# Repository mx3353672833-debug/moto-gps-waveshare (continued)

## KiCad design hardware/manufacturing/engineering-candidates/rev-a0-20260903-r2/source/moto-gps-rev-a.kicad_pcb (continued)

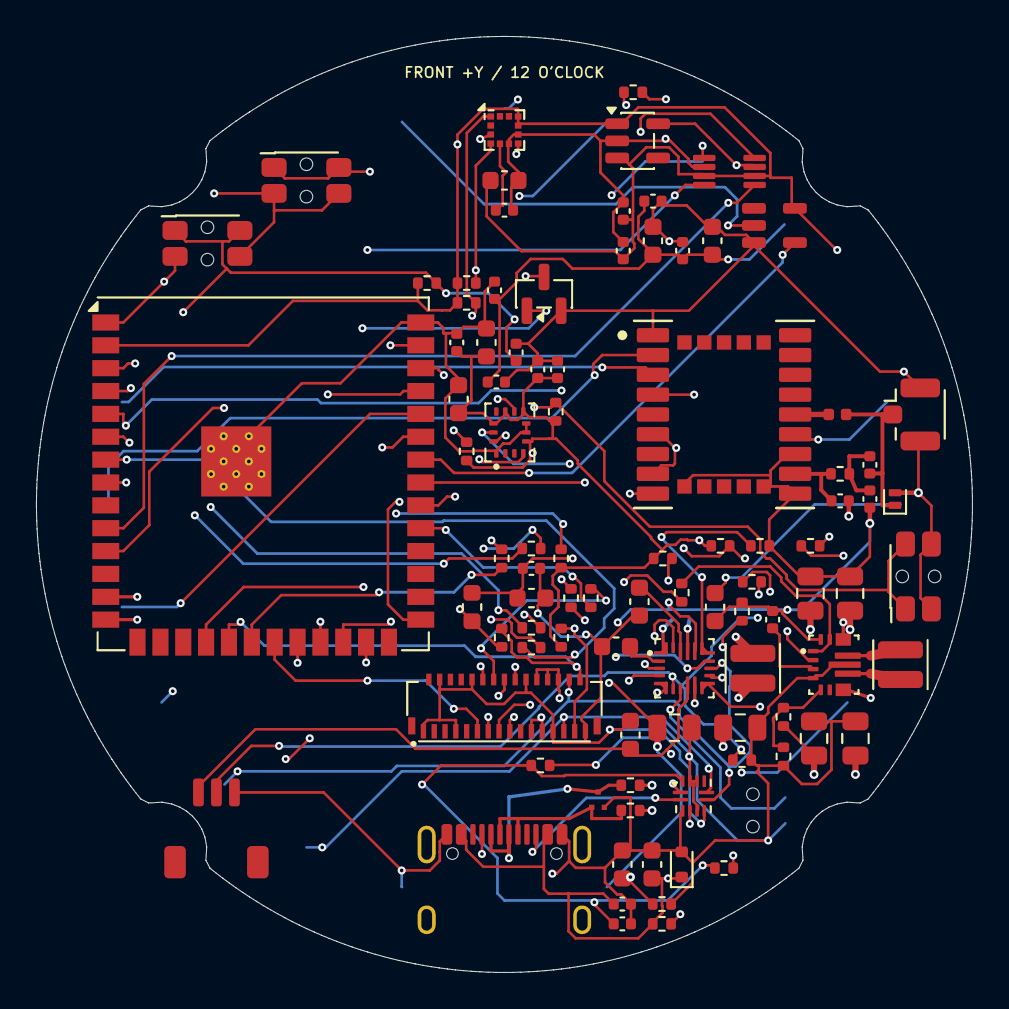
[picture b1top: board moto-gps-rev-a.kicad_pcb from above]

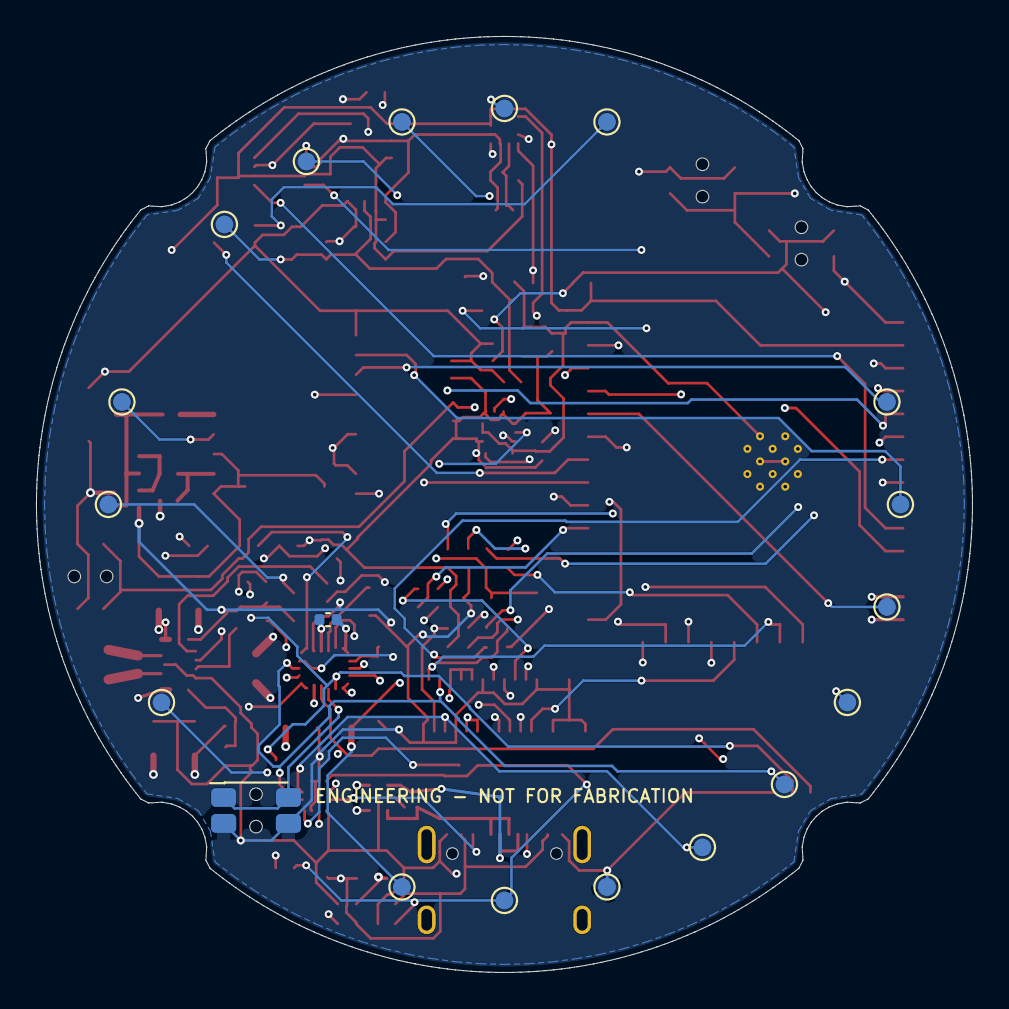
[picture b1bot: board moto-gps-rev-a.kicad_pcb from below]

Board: 4 copper layers, 52.0 x 52.0 mm, 112 parts (19 on the bottom side), 74 nets.

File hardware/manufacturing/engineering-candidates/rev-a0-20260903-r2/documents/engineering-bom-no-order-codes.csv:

"Comment","Designator","Footprint","Quantity","DNP"
"10uF/6.3V","C1,C19","Capacitor_SMD:C_0603_1608Metric","2",""
"100nF","C2,C5,C6,C18,C20,C22,C24,C29,C30,C35","Capacitor_SMD:C_0402_1005Metric","10",""
"4.7nF/1kV","C3","Capacitor_SMD:C_0603_1608Metric","1",""
"10uF/10V","C4,C9,C12","Capacitor_SMD:C_0603_1608Metric","3",""
"47nF/10V","C7","Capacitor_SMD:C_0402_1005Metric","1",""
"4.7uF/10V","C8","Capacitor_SMD:C_0603_1608Metric","1",""
"22uF/10V","C10,C11","Capacitor_SMD:C_0805_2012Metric","2",""
"1uF/25V","C13","Capacitor_SMD:C_0603_1608Metric","1",""
"10uF/10V","C14,C15","Capacitor_SMD:C_0805_2012Metric","2",""
"22uF/6.3V","C16,C17","Capacitor_SMD:C_0805_2012Metric","2",""
"1uF","C21,C27","Capacitor_SMD:C_0402_1005Metric","2",""
"2.2uF","C23,C25,C28","Capacitor_SMD:C_0603_1608Metric","3",""
"220nF","C26","Capacitor_SMD:C_0402_1005Metric","1",""
"100pF_C0G","C31","Capacitor_SMD:C_0402_1005Metric","1",""
"10uF","C34","Capacitor_SMD:C_0603_1608Metric","1",""
"100nF_VBCKP","C36","Capacitor_SMD:C_0402_1005Metric","1",""
"33pF_C0G","C37","Capacitor_SMD:C_0402_1005Metric","1",""
"ESD5Z5.0T1G","D1","Diode_SMD:D_SOD-523","1",""
"ESD3Z5V0BU_low-C","D2","Diode_SMD:D_SOD-882","1",""
"120R@100MHz_2A","FB1","Inductor_SMD:L_0603_1608Metric","1",""
"XKB_U262-16XN-4BVC11_CANDIDATE","J1","MOTO_GPS:USB_C_XKB_U262-16XN-4BVC11_MOTO_REVA","1",""
"1S_LiPo_10k_NTC_PROTECTED","J2","MOTO_GPS:JST_SH_SM03B-SRSS-TB_MOTO_REVA","1",""
"XUNPU_FPC-0.3FX-31PWBH10_CANDIDATE","J3","MOTO_GPS:XUNPU_FPC-0.3FX-31PWBH10","1",""
"U.FL_GNSS_ACTIVE_ANT","J4","MOTO_GPS:UFL_Hirose_UFL-R-SMT-1_MOTO_REVA","1",""
"1uH_4.2A_C492725","L1,L2","Inductor_SMD:L_Changjiang_FTC252012S","2",""
"68nH_high-SRF","L3","Inductor_SMD:L_0402_1005Metric","1",""
"2N7002","Q1","Package_TO_SOT_SMD:SOT-23","1",""
"0R","R1,R2,R3,R4,R5,R6","Resistor_SMD:R_0402_1005Metric","6",""
"10k","R7,R8,R9,R16,R17,R21,R22,R29,R30,R31","Resistor_SMD:R_0402_1005Metric","10",""
"1M","R12","Resistor_SMD:R_0402_1005Metric","1",""
"22R","R13,R14","Resistor_SMD:R_0402_1005Metric","2",""
"900k_1%","R15","Resistor_SMD:R_0402_1005Metric","1",""
"4.99k_1%_ILIM=501mA_typ","R18","Resistor_SMD:R_0402_1005Metric","1",""
"5.23k_1%","R19","Resistor_SMD:R_0402_1005Metric","1",""
"30.1k_1%","R20","Resistor_SMD:R_0402_1005Metric","1",""
"100k_default_charge_on","R23","Resistor_SMD:R_0402_1005Metric","1",""
"470k_1%","R24","Resistor_SMD:R_0402_1005Metric","1",""
"150k_1%","R25","Resistor_SMD:R_0402_1005Metric","1",""
"100k","R26,R32","Resistor_SMD:R_0402_1005Metric","2",""
"4.7k_EVT","R27,R28","Resistor_SMD:R_0402_1005Metric","2",""
"0R_RF_SERIES","R33","Resistor_SMD:R_0402_1005Metric","1",""
"100k_EN+PFM","R34","Resistor_SMD:R_0402_1005Metric","1",""
"POWER_QON","SW1","Button_Switch_SMD:SW_SPST_EVQP7C","1",""
"RESET","SW2","Button_Switch_SMD:SW_SPST_EVQP7C","1",""
"BOOT","SW3","Button_Switch_SMD:SW_SPST_EVQP7C","1",""
"FUNCTION","SW4","Button_Switch_SMD:SW_SPST_EVQP7C","1",""
"ESP32-S3-WROOM-1U-N16R8","U1","MOTO_GPS:ESP32-S3-WROOM-1U_MOTO_REVA","1",""
"BQ25628ERYKR","U2","MOTO_GPS:BQ25628E_RYK0018A","1",""
"TPS63070RNMR","U3","MOTO_GPS:TI_RNM0015A_VQFN-15","1",""
"TUSB320LAIRWBR","U4","Package_DFN_QFN:Texas_X2QFN-12_1.6x1.6mm_P0.4mm","1",""
"QMI8658C@0x6B","U5","MOTO_GPS:QMI8658C_LGA-14_2.5x3.0mm","1",""
"LIS2MDLTR@0x1E","U6","Package_LGA:LGA-12_2x2mm_P0.5mm","1",""
"TPS7A2030PDBVR","U7","Package_TO_SOT_SMD:SOT-23-5","1",""
"TXU0202DCUR","U8","MOTO_GPS:VSSOP-8_2.3x2mm_P0.5mm_NoSilk","1",""
"SN74LVC1G17DBVR","U9","MOTO_GPS:SOT-23-5_NoSilk","1",""
"LC76GABMD","U10","MOTO_GPS:Quectel_LC76GABMD_LCC18_LGA10","1",""
"TPD2EUSB30DRTR","U11","MOTO_GPS:Texas_DRT0003A_SON-3_1x1mm_P0.65mm_NoSilk","1",""
